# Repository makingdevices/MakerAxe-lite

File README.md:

<!-- Improved compatibility of back to top link: See: https://github.com/othneildrew/Best-README-Template/pull/73 -->

<!--
*** Thanks for checking out the Best-README-Template. If you have a suggestion
*** that would make this better, please fork the repo and create a pull request
*** or simply open an issue with the tag "enhancement".
*** Don't forget to give the project a star!
*** Thanks again! Now go create something AMAZING! :D
-->

<!-- PROJECT SHIELDS -->
<!--
*** I'm using markdown "reference style" links for readability.
*** Reference links are enclosed in brackets [ ] instead of parentheses ( ).
*** See the bottom of this document for the declaration of the reference variables
*** for contributors-url, forks-url, etc. This is an optional, concise syntax you may use.
*** https://www.markdownguide.org/basic-syntax/#reference-style-links
-->
[![Instagram][ig-shield]][ig-url]
[![Instagram][yt-shield]][yt-url]
[![PCBWAY][sponsor-shield]][sponsor-url]
[![Stargazers][stars-shield]][stars-url]
[![Issues][issues-shield]][issues-url]
[![LinkedIn][linkedin-shield]][linkedin-url]

<!-- PROJECT LOGO -->
<br />
<div align="center">

<h3 align="center">Making Devices</h3>

  <p align="center">
    Open Source projects where we struggle with engineering, electronics, coding and who knows what else... MakerAxe-lite is the foundation for new BTC miners and exciting hardware in the future. 
  </p>
</div>

<!-- TABLE OF CONTENTS -->
<details>
  <summary>Table of Contents</summary>
  <ol>
    <li>
      <a href="#about-the-project">About The Project</a>
      <ul>
        <li><a href="#built-with">Built With</a></li>
      </ul>
    </li>
    <li>
      <a href="#Build-one">Build one</a>
      <ul>
      </ul>
    </li>
    <li><a href="#goals">Goals</a></li>
    <li><a href="#features">Features</a></li>
    <li><a href="#roadmap">Roadmap</a></li>
    <li><a href="#license">License</a></li>
    <li><a href="#contact">Contact</a></li>
    <li><a href="#tools">Tools</a></li>
    <li><a href="#Sponsor">Sponsor</a></li>
  </ol>
</details>

<!-- ABOUT THE PROJECT -->
## About The Project

[![Bytes Counter Shot][product-screenshot]](https://makingdevices.com/)

```
Open Source is Intrinsic to Bitcoin
```

This is the motto you will see at the top of the [Bitaxe repository](https://github.com/skot/bitaxe), and it’s the reason Why MakerAxe-Lite was created.

MakerAxe Lite is the first attempt to extract the essentials of Bitaxe, reduce it to the minimum, and create a foundation for building new and exciting hardware in the future.

The project modifies the original hardware with the following changes:

1. The screen is not needed, as you now have AxeOS. Therefore, the screen will be removed (DNP) to reduce energy consumption and costs.
2. The 4-layer PCB is reduced to a 2-layer PCB, decreasing the cost of the PCB.
3. The 5V barrel input connector is replaced with USB PD. The voltage (20V, 15V, or 12V) is yet to be decided. This change ensures compatibility with recycled and reused phone or laptop chargers.
4. A LED has been added for blinking status and debug purposes.
5. Software compatibility with the stock [ESP-miner AxeOS](https://github.com/skot/ESP-Miner) (aside from the LED indicator).

<p align="right">(<a href="#readme-top">back to top</a>)</p>

### Built With

[![Microcontroller][ESP32]][ESP32-url]

[![Kicad][kicad-shield]][kicad-url]
[![SPONSOR][sponsor-icon]][sponsor-url]

<p align="right">(<a href="#readme-top">back to top</a>)</p>

<!-- GETTING STARTED -->

## Build one
The project is yet to be finished. Should you want to reproduce it, be careful. 

1. Get the gerber files for the latest version: [MakerAxe-lite V025](/Gerber/makeraxe-litev025.zip) 
2. Send them to a PCB manufacturer ([Our Sponsor is PCBWAY][sponsor-url])
3. Schematic (?)

YET TO BE COMPLETED.

<p align="right">(<a href="#readme-top">back to top</a>)</p>

<!-- GOALS -->
## Goals
- **Standalone**: can mine directly to your pool over WiFi. No External computer needed.
- **Embedded**: low cost, low maintenance, high availability, high reliability, low power.
- **ASIC**: based on the very, very efficient BM1366 from Bitmain.
- **Versatile**: solo/pool mining, autotune power/heat/efficiency.
- **Open Source**: All design files are provided.

<p align="right">(<a href="#readme-top">back to top</a>)</p>

<!-- FEATURES -->
## Features
- **ESP32-S3-WROOM-1** wifi microcontroller on board
- **TI TPS40305** buck regulator steps down the input voltage to power the BM1366
- **Maxim DS4432U+** current DAC digitally adjusts the BM1366 core voltage from 0.04V to 2.4V
- **TI INA260** power meter measures the input voltage and current of the miner
- **Microchip EMC2101** PWM controls the fan and monitors tach output. BM1366 doesn't support die temp, but we have it placed super close to the ASIC so we can use the internal temp feature.
- Enjoy :D!

<p align="right">(<a href="#readme-top">back to top</a>)</p>

<!-- ROADMAP -->
## Roadmap

- [X] Design the V025 prototype board.
- [ ] Complete the schematic and BoM files with LCSC&DK codes. 
- [ ] Order/Assembly the V025 prototype board.
- [ ] Validate V025 revision
  - [ ] Check that USB PD Works (12V, 15V, 20V)
  - [ ] Check the ESP32 can be programmed. 
  - [ ] AxeOS Self-testing is OK.
  - [ ] Solder the ASIC and check temperatures.
  - [ ] Characterize the overall efficiency.
  - [ ] Stress the buck converter to see if it is enough for next projects.
  - [ ] Explore alternatives to eliminate 5V rail.
  - [ ] Develop firmware so the LED can be used. Merge to ESP-miner if possible
- [ ] Validate the complete design + order PCBA 

See the [open issues](https://github.com/makingdevices/MakerAxe-lite/issues) for a full list of proposed features (and known issues).

State: Project <b>ONGOING</b> - 26/12/2024

Priority: <b>High</b>

<p align="right">(<a href="#readme-top">back to top</a>)</p>

<!-- LICENSE -->
## License

Distributed under three licenses:
- [Hardware](/License/HW_cern_ohl_s_v2.pdf)
- [Software](/License/SW_GPLv3.0.txt)
- [Documentation](/License/Documentation_CC-BY-SA-4.0.txt)

OSHWA License: Not Finished

[![GPL v3 License][license-shield]][license-url] 
<p align="right">(<a href="#readme-top">back to top</a>)</p>

<!-- CONTACT -->
## Contact

Making Devices - [@MakingDevices](https://www.instagram.com/makingdevices/)

Project Link: [https://github.com/makingdevices/MakerAxe-lite](https://github.com/makingdevices/MakerAxe-lite)

Other Links: [LinkTree](https://makingdevices.com/links/)

<!-- Tools -->
## Tools

During the realization of this project, you may need tools to assemble the PCB, solder components, and more.

These are the tools we've tested and currently have in our lab, so feel free to check them out if needed. Keep in mind that, even if prices are the same, you can support us in continuing to develop projects like this through the Amazon Influencer Program. Thank you!

- Microscope for smd soldering: [LinkMicro 246ms](https://amzn.to/3ZMVvwG)
- My solder paste: [ChipQuik LowTemp](https://amzn.to/3ZPYBjz)
- My soldering station with power supply: [Yihua 853D](https://amzn.to/3DwH0Wh)

<!-- Sponsor -->
## Sponsors

[PCBWAY](https://www.pcbway.com/?from=makingdevices) is the most professional PCB manufacturer for prototyping and low-volume production to work with in the world. With more than a decade in the field, They are committed to meeting the needs of their customers from different industries in terms of quality, delivery, cost-effectiveness and any other demanding requests. As Sponsor of Making Devices, they will be in charge of all the PCBs for MDV, allowing both of us to grow together in a long term partnership. We hope you take them into account for your both personal and professional prototypes or products.

[![Sponsor Shot][sponsor-pcb-1]][sponsor-url]

<p align="right">(<a href="#readme-top">back to top</a>)</p>

<!-- MARKDOWN LINKS & IMAGES -->
<!-- https://www.markdownguide.org/basic-syntax/#reference-style-links -->
[contributors-shield]: https://img.shields.io/github/contributors/makingdevices/MakerAxe-lite.svg?style=for-the-badge
[contributors-url]: https://github.com/makingdevices/MakerAxe-lite/graphs/contributors
[forks-shield]: https://img.shields.io/github/forks/makingdevices/MakerAxe-lite.svg?style=for-the-badge
[forks-url]: https://github.com/makingdevices/MakerAxe-lite/network/members
[stars-shield]: https://img.shields.io/github/stars/makingdevices/MakerAxe-lite.svg?style=for-the-badge
[stars-url]: https://github.com/makingdevices/MakerAxe-lite/stargazers
[issues-shield]: https://img.shields.io/github/issues/makingdevices/MakerAxe-lite.svg?style=for-the-badge
[issues-url]: https://github.com/makingdevices/MakerAxe-lite/issues
[license-shield]: /images/license.png
[license-url]: https://github.com/makingdevices/MakerAxe-lite/tree/main/License
[linkedin-shield]: https://img.shields.io/badge/-LinkedIn-black.svg?style=for-the-badge&logo=linkedin&colorB=555
[linkedin-url]: https://www.linkedin.com/company/making-devices/
[sponsor-shield]: https://img.shields.io/badge/SPONSOR-PCBWAY-black.svg?style=for-the-badge&colorB=1200
[sponsor-url]: https://www.pcbway.com/?from=makingdevices
[sponsor-screenshot]: /images/PCB_sponsor.png
[sponsor-pcb-1]: /images/makeraxe_pcb1.jpg
[sponsor-wurth-1]: /images/wurth_1.gif
[sponsor-wurth-3]: /images/wurth_3.jpg
[sponsor-url-wurth]: https://www.we-online.com/en
[product-screenshot]: images/render_front_pcb.png
[ESP32]: https://img.shields.io/badge/ESP32_S3-7c0a02?style=for-the-badge
[ESP32-url]: https://www.espressif.com/sites/default/files/documentation/esp32-s3-wroom-1_wroom-1u_datasheet_en.pdf
[kicad-shield]: https://img.shields.io/badge/kicad-0b03fc?style=for-the-badge&logo=kicad&logoColor=white
[kicad-url]: https://www.kicad.org/
[YT-screenshot]: images/YT_assembly.PNG
[sponsor-icon]:  https://img.shields.io/badge/-PCBWAY-black.svg?style=for-the-badge&colorB=1200
[ig-shield]: https://img.shields.io/badge/instagram-a83297?style=for-the-badge&logo=instagram&logoColor=white
[ig-url]: https://www.instagram.com/makingdevices/
[yt-shield]: https://img.shields.io/badge/youtube-ff0000?style=for-the-badge&logo=youtube&logoColor=white
[yt-url]: https://www.youtube.com/@MakingDevices
[MPLAB-C]: https://img.shields.io/badge/MPLAB%20C18-DD0031?style=for-the-badge&logo=C&logoColor=white
[Arduino]: https://img.shields.io/badge/ARDUINO-00878F?style=for-the-badge&logo=arduino&logoColor=white
[wurth-icon]: https://img.shields.io/badge/Wurth%20elektronik-FF0031?style=for-the-badge&logoColor=white
[Arduino-url]: https://www.arduino.cc/
[MPLAB-C-url]: https://www.microchip.com/en-us/development-tool/SW006011
[Svelte.dev]: https://img.shields.io/badge/Svelte-4A4A55?style=for-the-badge&logo=svelte&logoColor=FF3E00
[Svelte-url]: https://svelte.dev/
[Laravel.com]: https://img.shields.io/badge/Laravel-FF2D20?style=for-the-badge&logo=laravel&logoColor=white
[Laravel-url]: https://laravel.com
[Bootstrap.com]: https://img.shields.io/badge/Bootstrap-563D7C?style=for-the-badge&logo=bootstrap&logoColor=white
[Bootstrap-url]: https://getbootstrap.com
[JQuery.com]: https://img.shields.io/badge/jQuery-0769AD?style=for-the-badge&logo=jquery&logoColor=white
[JQuery-url]: https://jquery.com

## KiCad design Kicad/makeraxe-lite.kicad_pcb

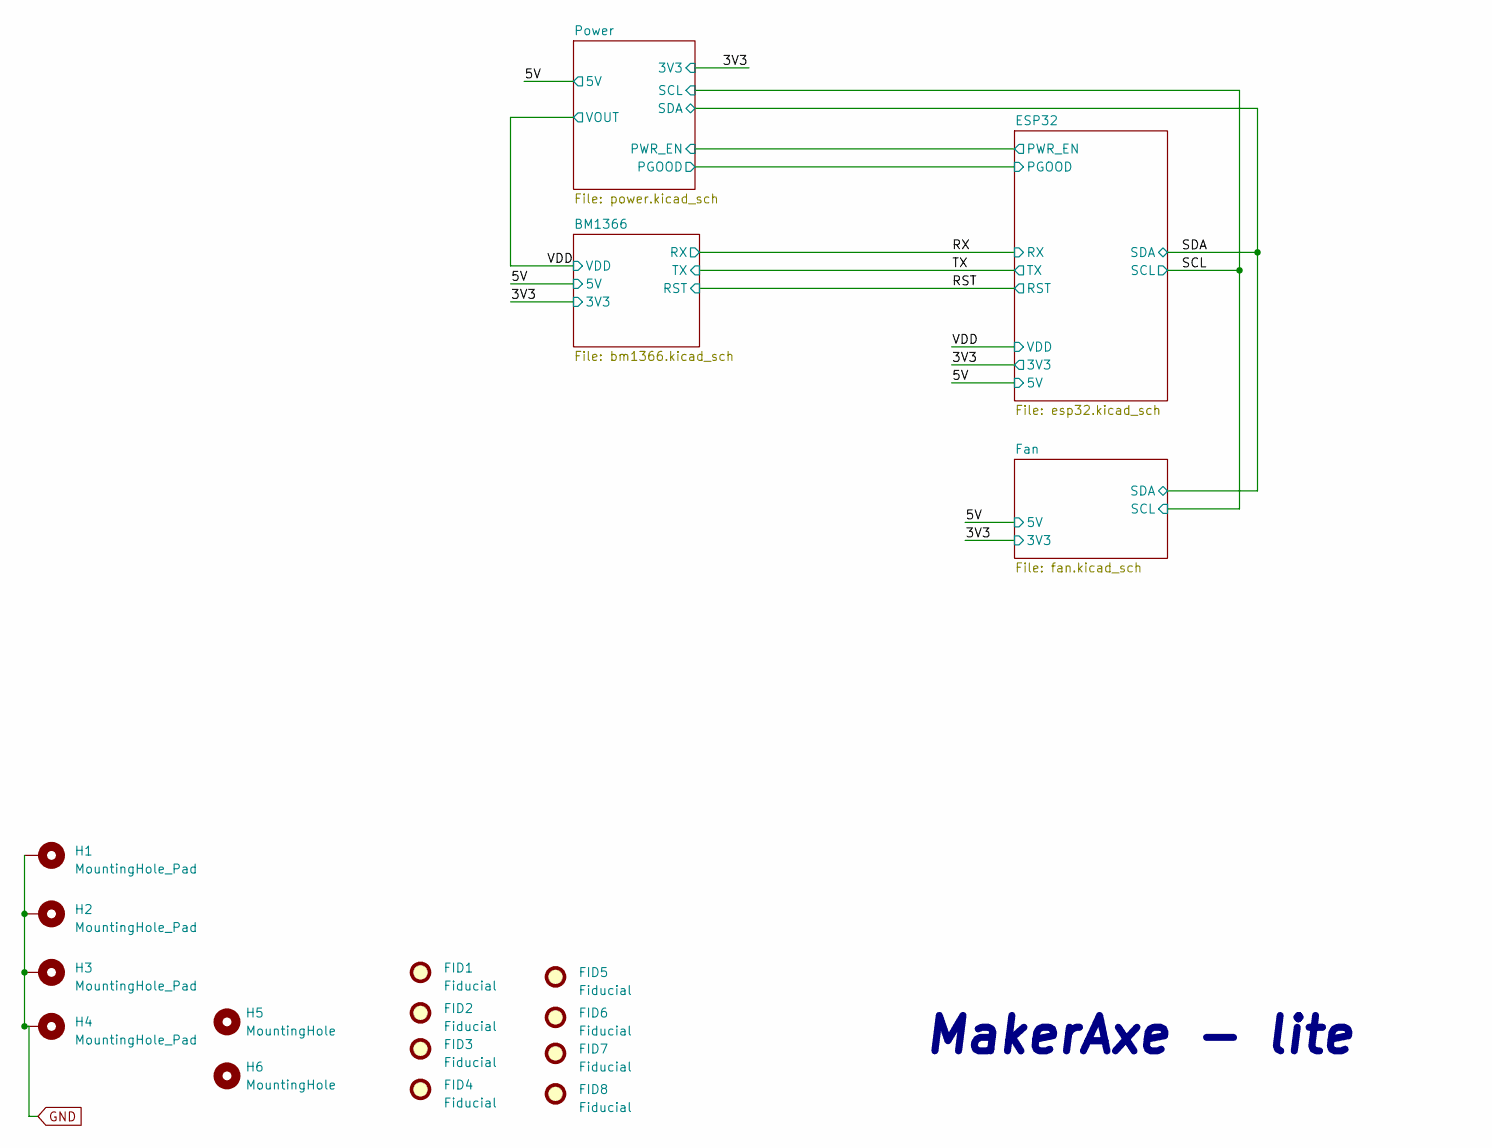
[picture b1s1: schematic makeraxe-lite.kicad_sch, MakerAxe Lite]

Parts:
FID1, FID2, FID3, FID4, FID5, FID6, FID7, FID8: Fiducial; Fiducial_1mm_Mask2mm
H1, H2, H3, H4: MountingHole_Pad; MountingHole_3mm_Pad_Via
H5, H6: MountingHole; MountingHole_3.5mm

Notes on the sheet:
MakerAxe - lite

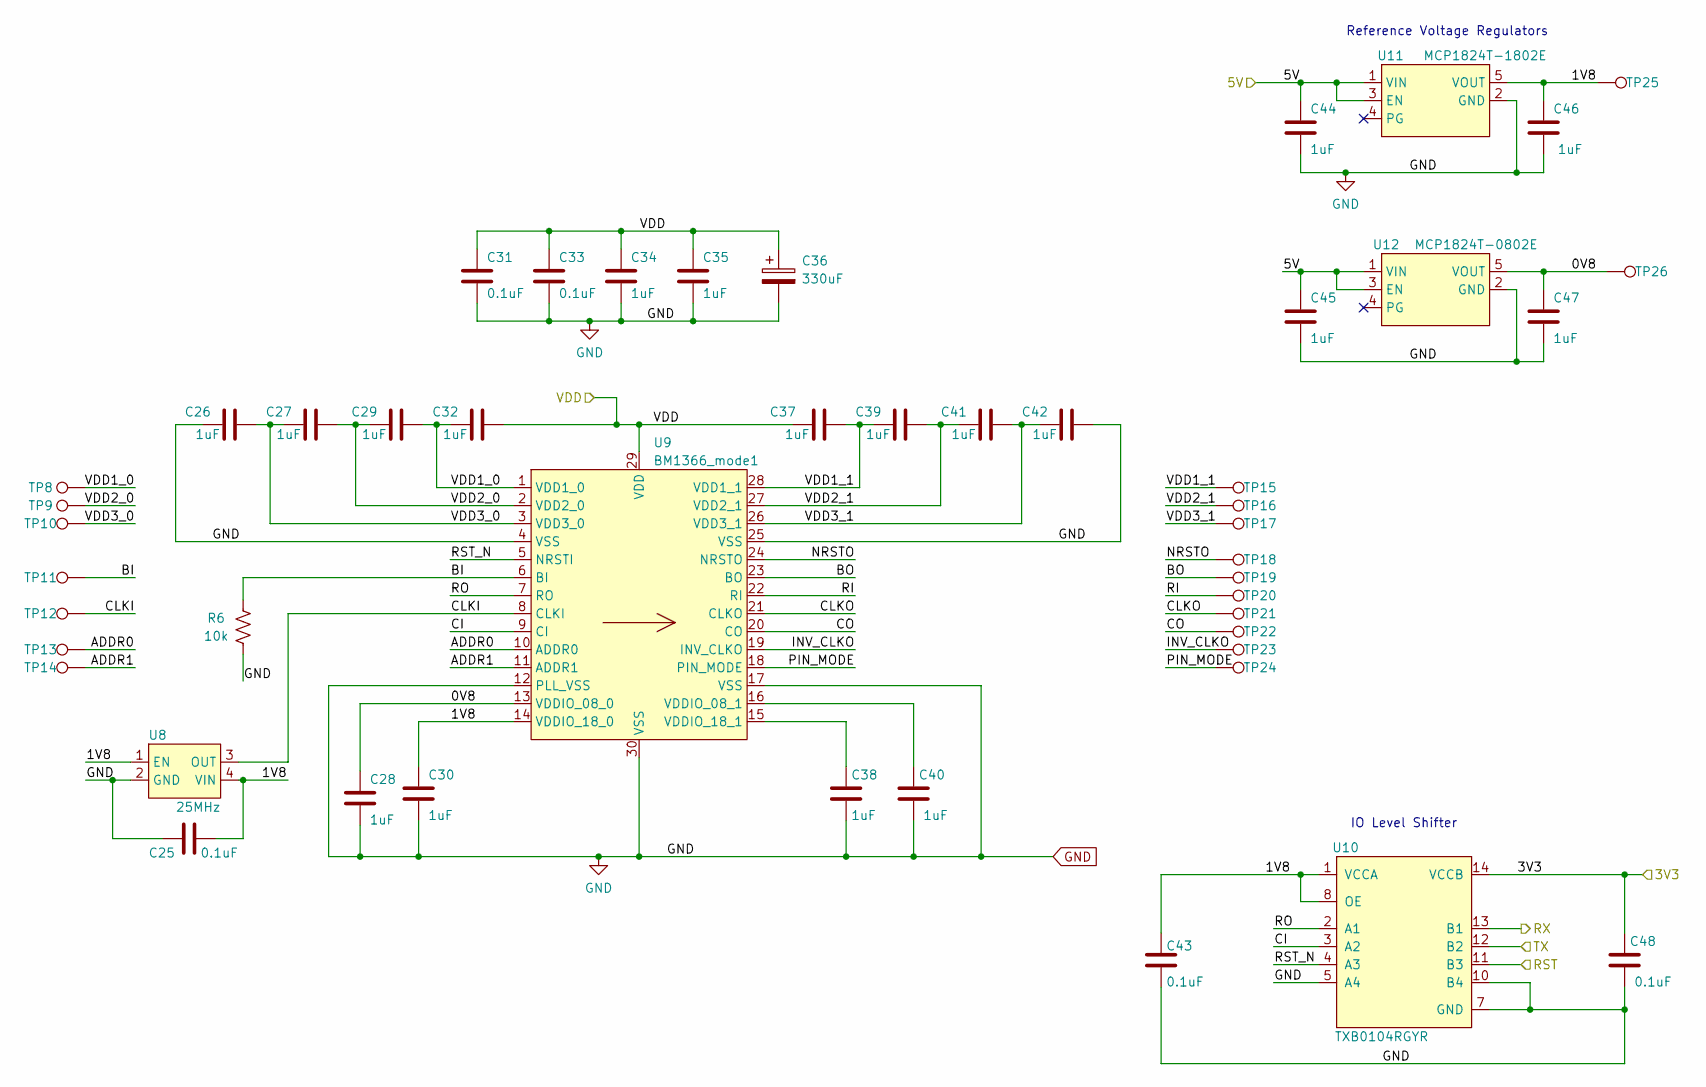
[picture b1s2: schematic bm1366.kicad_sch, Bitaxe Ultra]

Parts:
C25, C31, C33, C43, C48: 0.1uF; C_0402_1005Metric; PARTNO 0402X104K100CT
C26, C27, C28, C29, C30, C32, C34, C35, C37, C38, C39, C40, C41, C42, C44, C45, C46, C47: 1uF; C_0402_1005Metric; PARTNO EMK105BJ105MV-F
C36: 330uF; CP_EIA-7343-31_Kemet-D_Pad2.25x2.55mm_HandSolder; PARTNO 293D337X9010E2TE3
R6: 10k; R_0402_1005Metric; PARTNO RC0402JR-0710KL
TP8, TP9, TP10, TP11, TP12, TP13, TP14, TP15, TP16, TP17, TP18, TP19, TP20, TP21, TP22, TP23, TP24, TP25, TP26: TestPoint; TestPoint_Pad_D1.5mm
U8: 25MHz; O 25,0-JO32-B-1V3-1-T1-LF; PARTNO O 25,0-JO32-B-1V3-1-T1-LF
U9: BM1366_mode1; BM1366
U10: TXB0104RGYR; TXB0104; PARTNO TXB0104RGYR
U11: MCP1824T-1802E; SOT-23-5; PARTNO MCP1824T-1802E/OT
U12: MCP1824T-0802E; SOT-23-5; PARTNO MCP1824T-0802E/OT

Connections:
/3V3: C48.1, U10.14 (VCCB); also elsewhere on the board
/5V: C44.1, C45.1, U11.1 (VIN), U11.3 (EN), U12.1 (VIN), U12.3 (EN); also elsewhere on the board
/BM1366/0V8: C28.1, C47.1, TP26.1, U9.13 (VDDIO_08_0), U12.5 (VOUT)
/BM1366/1V8: C25.2, C30.1, C43.1, C46.1, TP25.1, U8.1 (EN), U8.4 (VIN), U9.14 (VDDIO_18_0), U10.1 (VCCA), U10.8 (OE), U11.5 (VOUT)
/BM1366/ADDR0: TP13.1, U9.10 (ADDR0)
/BM1366/ADDR1: TP14.1, U9.11 (ADDR1)
/BM1366/BO: TP19.1, U9.23 (BO)
/BM1366/CI: U9.9 (CI), U10.3 (A2)
/BM1366/CLKI: TP12.1, U8.3 (OUT), U9.8 (CLKI)
/BM1366/CLKO: TP21.1, U9.21 (CLKO)
/BM1366/CO: TP22.1, U9.20 (CO)
/BM1366/INV_CLKO: TP23.1, U9.19 (INV_CLKO)
/BM1366/NRSTO: TP18.1, U9.24 (NRSTO)
/BM1366/PIN_MODE: TP24.1, U9.18 (PIN_MODE)
/BM1366/RI: TP20.1, U9.22 (RI)
/BM1366/RO: U9.7 (RO), U10.2 (A1)
/BM1366/RST_N: U9.5 (NRSTI), U10.4 (A3)
/BM1366/VDD1_0: C29.2, C32.1, TP8.1, U9.1 (VDD1_0)
/BM1366/VDD1_1: C37.2, C39.1, TP15.1, U9.28 (VDD1_1)
/BM1366/VDD2_0: C27.2, C29.1, TP9.1, U9.2 (VDD2_0)
/BM1366/VDD2_1: C39.2, C41.1, TP16.1, U9.27 (VDD2_1)
/BM1366/VDD3_0: C26.2, C27.1, TP10.1, U9.3 (VDD3_0)
/BM1366/VDD3_1: C41.2, C42.1, TP17.1, U9.26 (VDD3_1)
/RST: U10.11 (B3); also elsewhere on the board
/RX: U10.13 (B1); also elsewhere on the board
/TX: U10.12 (B2); also elsewhere on the board
unnamed: C40.1, U9.16 (VDDIO_08_1)
unnamed: C38.1, U9.15 (VDDIO_18_1)

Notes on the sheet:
Reference Voltage Regulators
IO Level Shifter

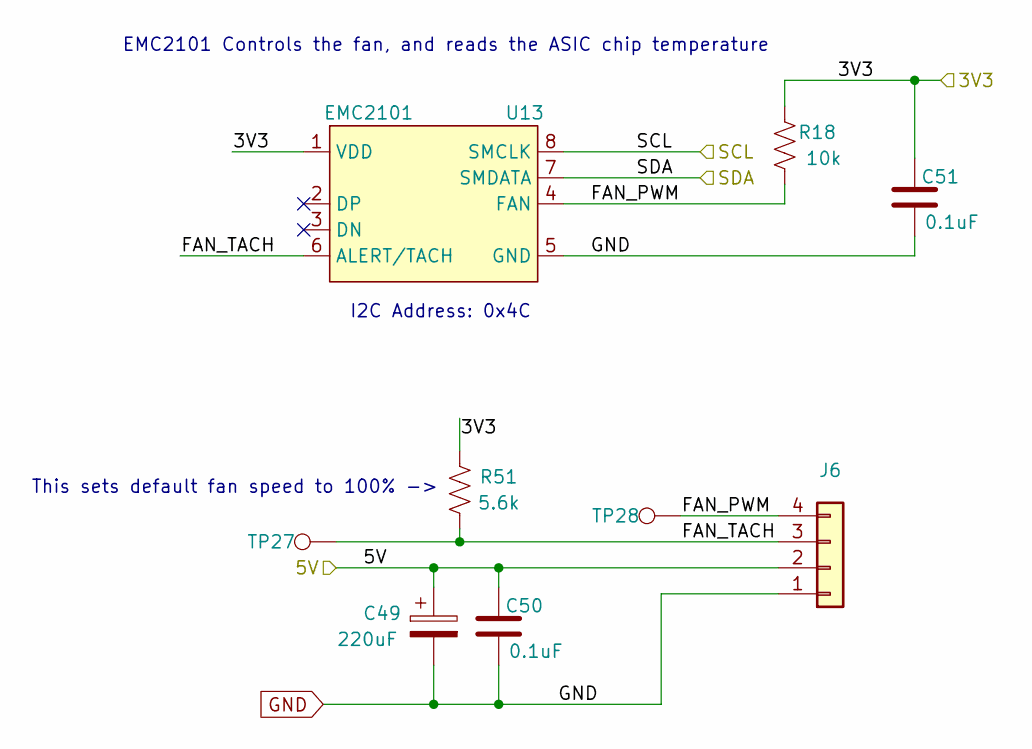
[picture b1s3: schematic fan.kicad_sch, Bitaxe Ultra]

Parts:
C49: 220uF; CP_Elec_6.3x7.7; PARTNO 865080345012
C50, C51: 0.1uF; C_0402_1005Metric; PARTNO 0402X104K100CT
J6: Conn_01x04; 470531000; PARTNO 0470531000
R18: 10k; R_0402_1005Metric; PARTNO RC0402JR-0710KL
R51: 5.6k; R_0402_1005Metric; PARTNO RC0402FR-135K6L
TP27, TP28: TestPoint; TestPoint_Pad_D1.5mm
U13: EMC2101; TSSOP-8_3x3mm_P0.65mm; PARTNO EMC2101-R-ACZL-TR

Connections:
/3V3: C51.1, R18.2, U13.1 (VDD); also elsewhere on the board
/5V: C49.1, C50.1, J6.2; also elsewhere on the board
/Fan/FAN_PWM: J6.4, R18.1, TP28.1, U13.4 (FAN)
/Fan/FAN_TACH: J6.3, TP27.1, U13.6 (ALERT/TACH); also elsewhere on the board
/SCL: U13.8 (SMCLK); also elsewhere on the board
/SDA: U13.7 (SMDATA); also elsewhere on the board

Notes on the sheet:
EMC2101 Controls the fan, and reads the ASIC chip temperature
This sets default fan speed to 100% ->
I2C Address: 0x4C

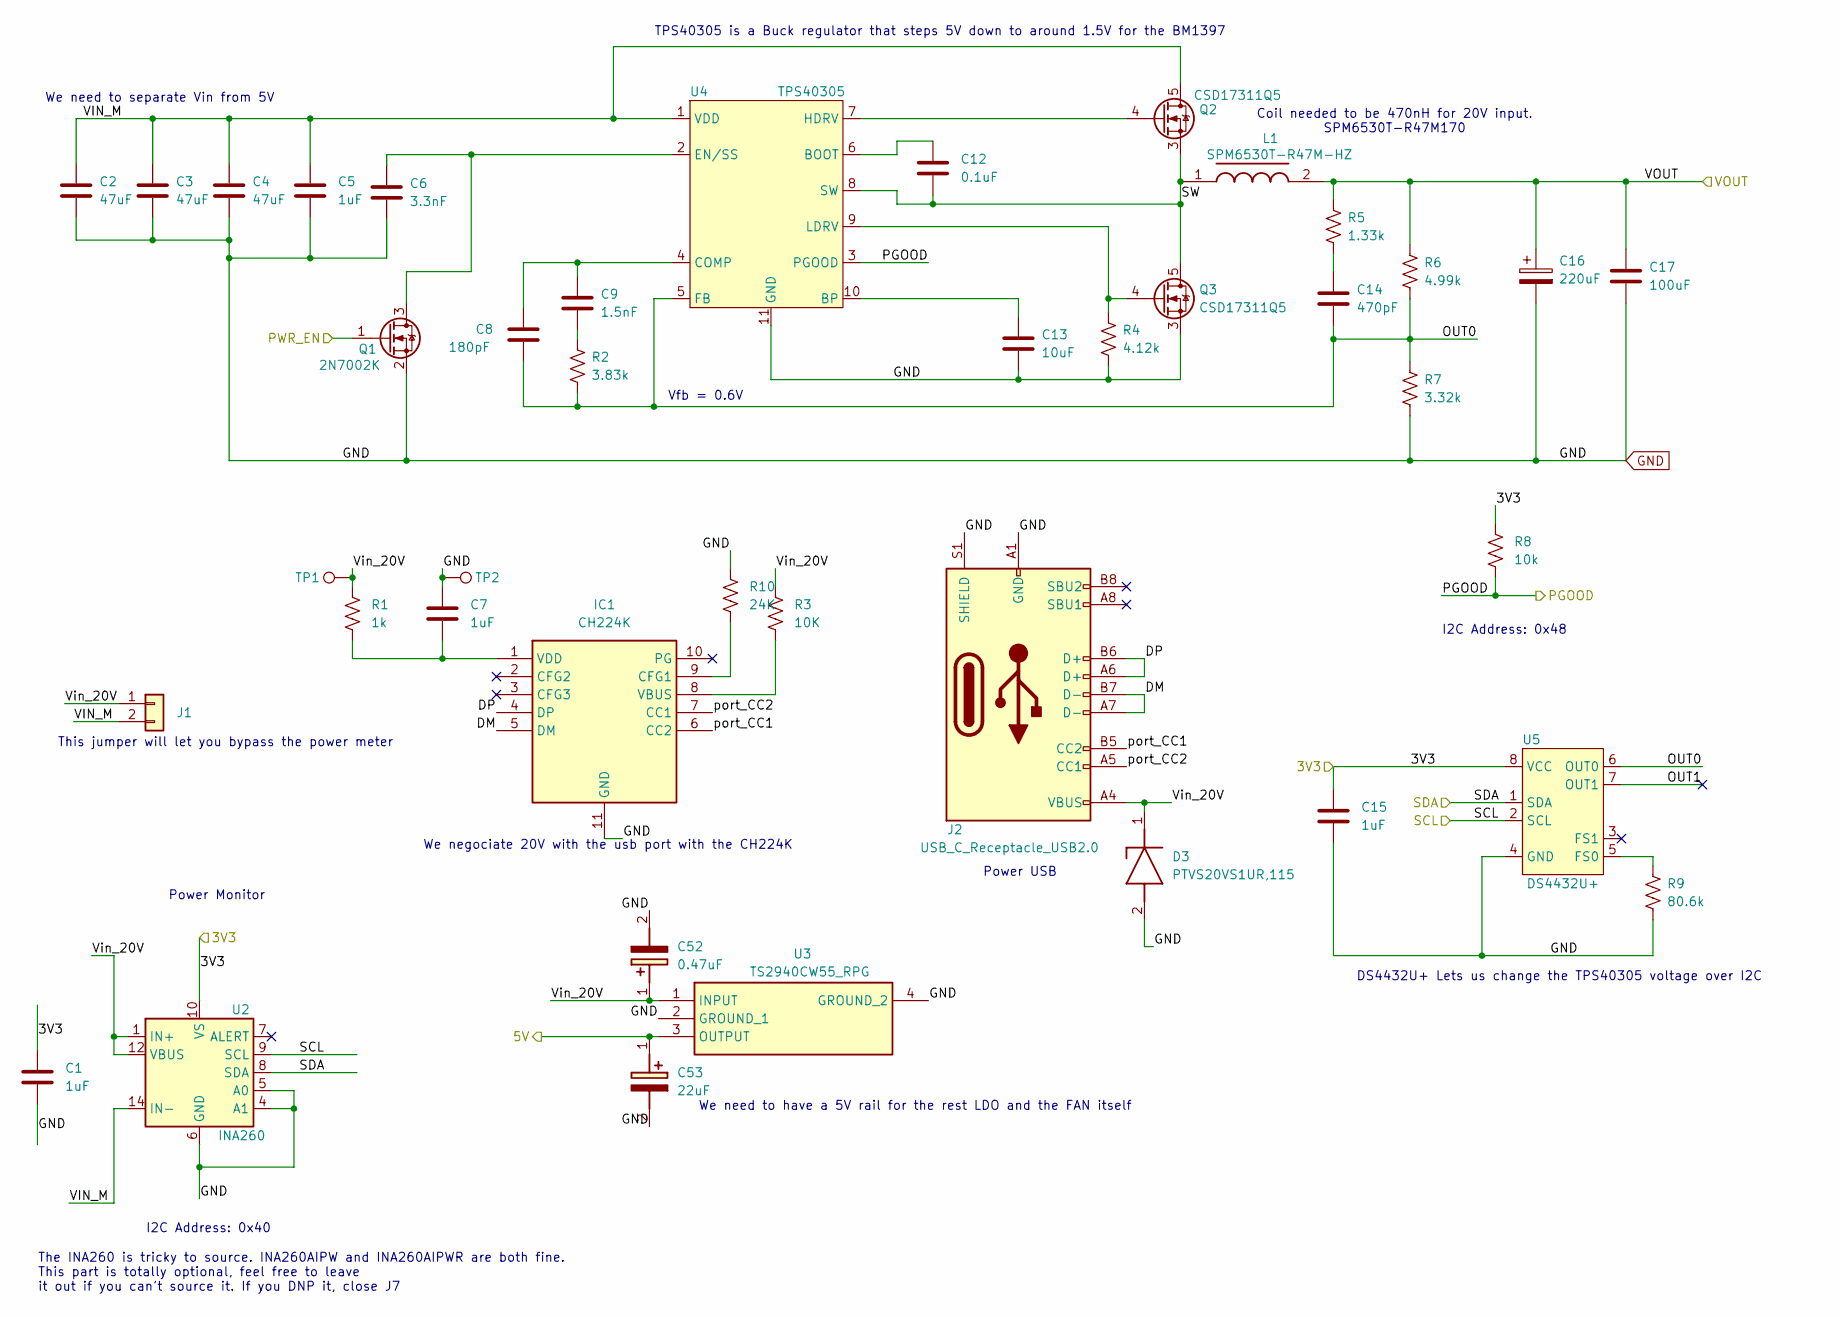
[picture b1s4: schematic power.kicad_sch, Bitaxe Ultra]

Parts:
C1, C15: 1uF; C_0402_1005Metric; PARTNO EMK105BJ105MV-F
C2, C3, C4: 47uF; C_1210_3225Metric; PARTNO GRM32ER61C476KE15L
C5, C7: 1uF; C_0805_2012Metric; PARTNO CL21B105KOFNNNG
C6: 3.3nF; C_0402_1005Metric; PARTNO CL05B332KB5NNNC
C8: 180pF; C_0805_2012Metric; PARTNO CC0805JRNPO9BN181
C9: 1.5nF; C_0805_2012Metric; PARTNO CC0805KRX7R9BB152
C12: 0.1uF; C_0402_1005Metric; PARTNO 0402X104K100CT
C13: 10uF; C_0805_2012Metric; PARTNO CL21A106KOQNNNE
C14: 470pF; C_0805_2012Metric; PARTNO 0805B471K500CT
C16: 220uF; CAP_2R5TPE220MAFB; PARTNO 2R5TPE220MAFB
C17: 100uF; C_1206_3216Metric; PARTNO C3216X5R0J107M160AB
C52: 0.47uF; T491A; Mouser Part Number 80-T491A474K025AT
C53: 22uF; T495C; Mouser Part Number 80-T495C226K25E300
D3: PTVS20VS1UR,115; SOD123W; Mouser Part Number 771-PTVS20VS1UR115
IC1: CH224K; SOP100P600X180-11N; Manufacturer_Part_Number CH224K
J1: Conn_01x02; PinHeader_1x02_P2.54mm_Vertical
J2: USB_C_Receptacle_USB2.0; USB_C_Receptacle_GCT_USB4105-xx-A_16P_TopMnt_Horizontal; PARTNO USB4105-GF-A
L1: SPM6530T-R47M-HZ; SPM6530; Mouser Part Number 810-SPM6530T-R47M-HZ
Q1: 2N7002K; SOT-323_SC-70; PARTNO 2N7002KW
Q2, Q3: CSD17311Q5; PARTNO CSD17311Q5
R1: 1k; R_0402_1005Metric; PARTNO RC0402FR-073K83L
R2: 3.83k; R_0402_1005Metric; PARTNO RC0402FR-073K83L
R3: 10K; R_0402_1005Metric; PARTNO RC0402FR-073K83L
R4: 4.12k; R_0402_1005Metric; PARTNO RMCF0402FT4K12
R5: 1.33k; R_0402_1005Metric; PARTNO RC0402FR-071K33L
R6: 4.99k; R_0402_1005Metric; PARTNO RC0402FR-074K99L
R7: 3.32k; R_0402_1005Metric; PARTNO RC0402FR-073K32L
R8: 10k; R_0402_1005Metric; PARTNO RC0402JR-0710KL
R9: 80.6k; R_0402_1005Metric; PARTNO RC0402FR-0780K6L
R10: 24K; R_0402_1005Metric; PARTNO RC0402FR-073K83L
TP1, TP2: TestPoint; TestPoint_Pad_D1.5mm
U2: INA260; TSSOP-16_4.4x5mm_P0.65mm; PARTNO INA260AIPW
U3: TS2940CW55_RPG; TO-263-3_TabPin2; Mouser Part Number 821-TS2940CW33RPG
U4: TPS40305; PARTNO TPS40305DRCR
U5: DS4432U+; TSSOP-8_3x3mm_P0.65mm; PARTNO DS4432U+

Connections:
/3V3: C1.1, C15.1, R8.1, U2.10 (VS), U5.8 (VCC); also elsewhere on the board
/5V: C53.1 (+), U3.3 (OUTPUT); also elsewhere on the board
/ESP32/PWR_EN: Q1.1 (G); also elsewhere on the board
/Power/DM: IC1.5 (DM), J2.A7 (D-), J2.B7 (D-)
/Power/DP: IC1.4 (DP), J2.A6 (D+), J2.B6 (D+)
/Power/OUT1: U5.7 (OUT1)
/Power/PGOOD: R8.2, U4.3 (PGOOD); also elsewhere on the board
/Power/SW: C12.2, L1.1, Q2.1, Q2.2, Q2.3 (S), Q3.5 (D), U4.8 (SW)
/Power/VIN_M: C2.1, C3.1, C4.1, C5.1, J1.2, Q2.5 (D), U2.14 (IN-), U2.15 (IN-), U2.16 (IN-), U4.1 (VDD)
/Power/Vin_20V: C52.1 (+), D3.1 (K), J1.1, J2.A4 (VBUS), J2.A9 (VBUS), J2.B4 (VBUS), J2.B9 (VBUS), R1.1, R3.1, TP1.1, U2.1 (IN+), U2.2 (IN+), U2.3 (IN+), U2.12 (VBUS), U3.1 (INPUT)
/Power/port_CC1: IC1.6 (CC2), J2.B5 (CC2)
/Power/port_CC2: IC1.7 (CC1), J2.A5 (CC1)
/SCL: U2.9 (SCL), U5.2 (SCL); also elsewhere on the board
/SDA: U2.8 (SDA), U5.1 (SDA); also elsewhere on the board
unnamed: C9.2, R2.1
unnamed: C14.1, R5.2
unnamed: IC1.9 (CFG1), R10.2
unnamed: IC1.8 (VBUS), R3.2
unnamed: C7.2, IC1.1 (VDD), R1.2
unnamed: C6.1, Q1.3 (D), U4.2 (EN/SS)
unnamed: Q2.4 (G), U4.7 (HDRV)
unnamed: Q3.4 (G), R4.1, U4.9 (LDRV)
unnamed: C12.1, U4.6 (BOOT)
unnamed: C13.1, U4.10 (BP)
unnamed: C8.1, C9.1, U4.4 (COMP)
unnamed: R9.1, U5.5 (FS0)

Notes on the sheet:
DS4432U+ Lets us change the TPS40305 voltage over I2C
I2C Address: 0x48
The INA260 is tricky to source. INA260AIPW and INA260AIPWR are both fine. This part is totally optional, feel free to leave it out if you can't source it. If you DNP it, close J7
Power Monitor
Power USB
TPS40305 is a Buck regulator that steps 5V down to around 1.5V for the BM1397
We need to have a 5V rail for the rest LDO and the FAN itself
Coil needed to be 470nH for 20V input. SPM6530T-R47M170
I2C Address: 0x40
Vfb = 0.6V
This jumper will let you bypass the power meter
We negociate 20V with the usb port with the CH224K
We need to separate Vin from 5V

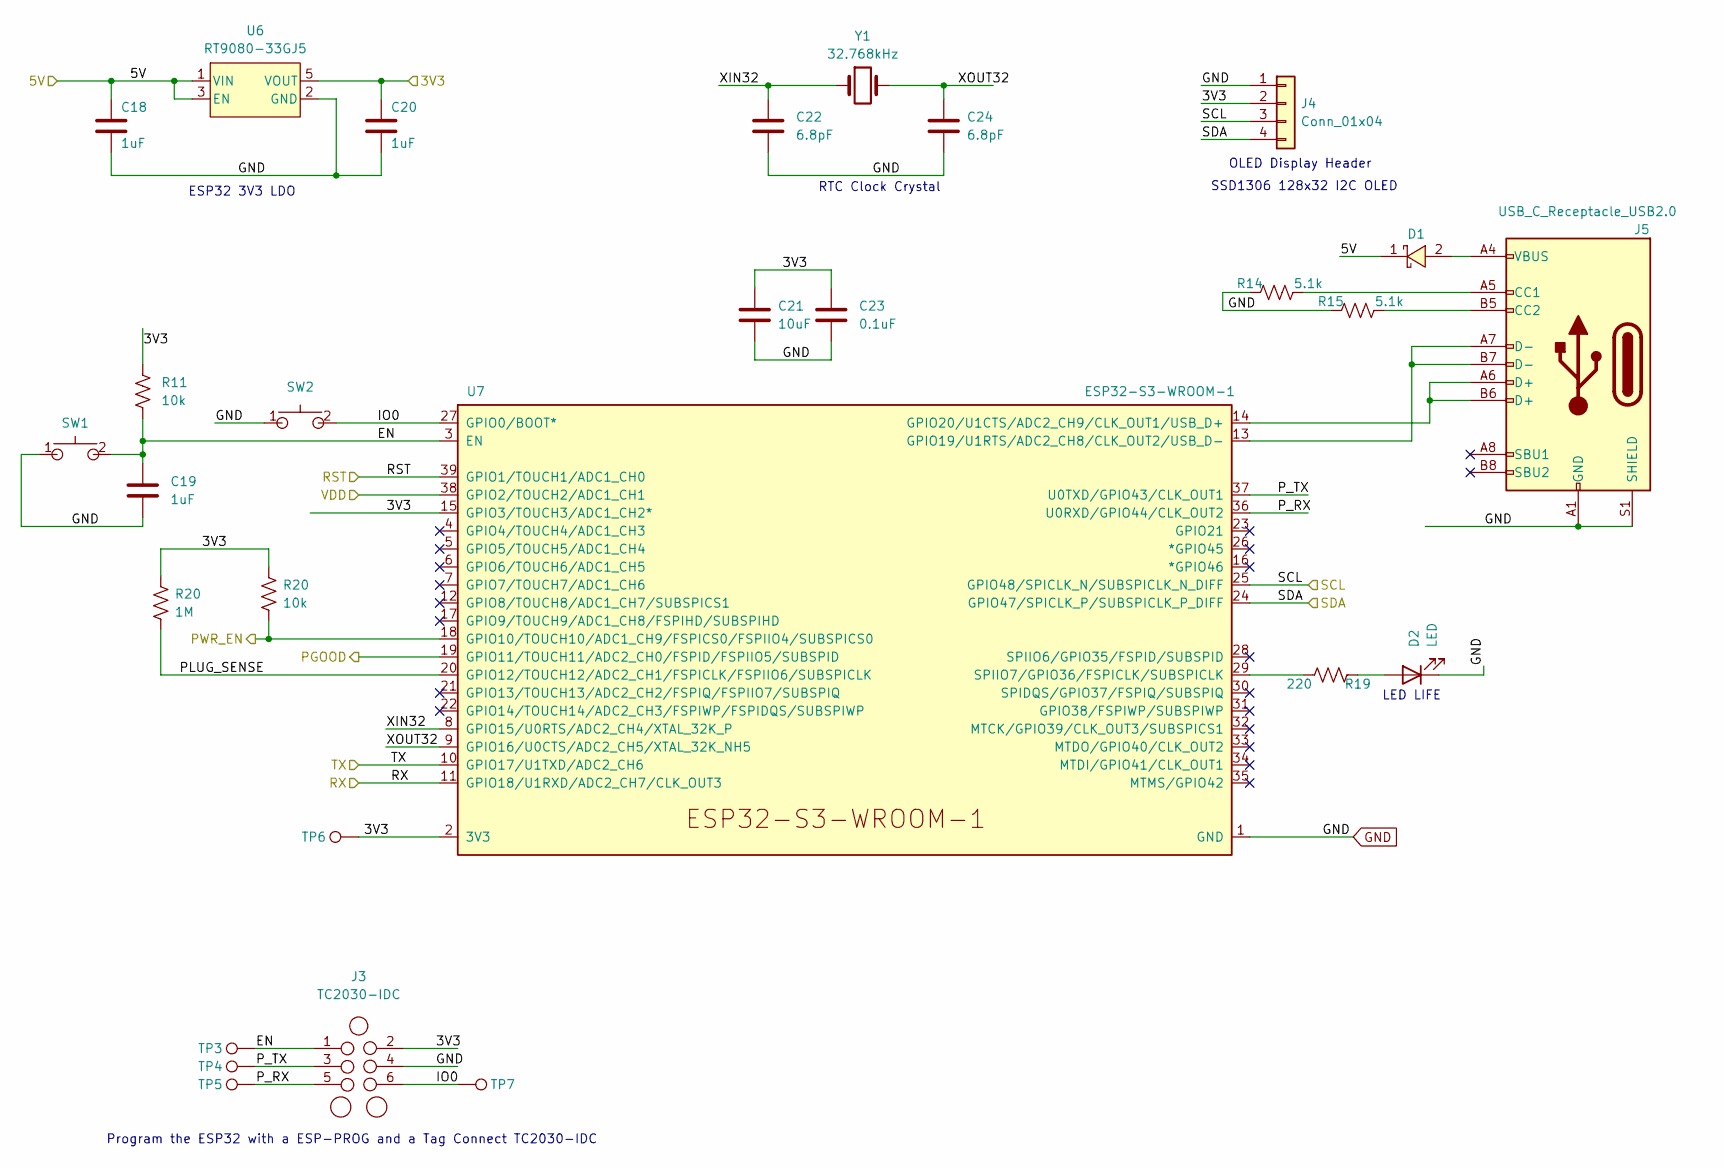
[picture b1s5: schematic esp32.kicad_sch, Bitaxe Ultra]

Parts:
C18, C19, C20: 1uF; C_0402_1005Metric; PARTNO EMK105BJ105MV-F
C21: 10uF; C_0805_2012Metric; PARTNO CL21A106KOQNNNE
C22, C24: 6.8pF; C_0402_1005Metric; PARTNO C0402C689C5GAC7867
C23: 0.1uF; C_0402_1005Metric; PARTNO 0402X104K100CT
D1: SS310; D_SMA; PARTNO SK310A-LTP
D2: LED; LED_0805_2012Metric_Pad1.15x1.40mm_HandSolder
J3: TC2030-IDC; Tag-Connect_TC2030-IDC-NL_2x03_P1.27mm_Vertical
J4: Conn_01x04; PinSocket_1x04_P2.54mm_Vertical_SMD_Pin1Right; PARTNO NPTC041KFXC-RC
J5: USB_C_Receptacle_USB2.0; USB_C_Receptacle_GCT_USB4105-xx-A_16P_TopMnt_Horizontal; PARTNO USB4105-GF-A
R11: 10k; R_0402_1005Metric; PARTNO RC0402JR-0710KL
R14, R15: 5.1k; R_0402_1005Metric; PARTNO RMCF0402JT5K10
R19: 220; R_0402_1005Metric; PARTNO RMCF0402JT5K10
R20: 1M; R_0402_1005Metric; PARTNO RC0402FR-071ML
SW1, SW2: GT-TC029B-H025-L1N; SW_CS1213AGF260_CRS; PARTNO CS1213AGF260
TP3, TP4, TP5, TP6, TP7: TestPoint; TestPoint_Pad_D1.5mm
U6: RT9080-33GJ5; PARTNO RT9080-33GJ5
U7: ESP32-S3-WROOM-1; PARTNO ESP32-S3-WROOM-1-N16R8
Y1: 32.768kHz; SC32S-7PF20PPM; PARTNO SC32S-7PF20PPM

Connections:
/3V3: C20.1, C21.1, C23.1, J3.2, J4.2, R11.1, TP6.1, U6.5 (VOUT), U7.2 (3V3), U7.15 (GPIO3/TOUCH3/ADC1_CH2*); also elsewhere on the board
/5V: C18.1, D1.1, U6.1 (VIN), U6.3 (EN); also elsewhere on the board
/ESP32/EN: C19.1, J3.1, R11.2, SW1.2, TP3.1, U7.3 (EN)
/ESP32/IO0: J3.6, SW2.2, TP7.1, U7.27 (GPIO0/BOOT*)
/ESP32/PLUG_SENSE: U7.20 (GPIO12/TOUCH12/ADC2_CH1/FSPICLK/FSPIIO6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); also elsewhere on the board
/ESP32/PWR_EN: U7.18 (GPIO10/TOUCH10/ADC1_CH9/FSPICS0/FSPIIO4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); also elsewhere on the board
/ESP32/P_RX: J3.5, TP5.1, U7.36 (U0RXD/GPIO44/CLK_OUT2)
/ESP32/P_TX: J3.3, TP4.1, U7.37 (U0TXD/GPIO43/CLK_OUT1)
/ESP32/XIN32: C22.1, U7.8 (GPIO15/U0RTS/ADC2_CH4/XTAL_32K_P), Y1.1
/ESP32/XOUT32: C24.1, U7.9 (GPIO16/U0CTS/ADC2_CH5/XTAL_32K_NH5), Y1.2
/Power/PGOOD: U7.19 (GPIO11/TOUCH11/ADC2_CH0/FSPID/FSPIIO5/S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); also elsewhere on the board
/RST: U7.39 (GPIO1/TOUCH1/ADC1_CH0); also elsewhere on the board
/RX: U7.11 (GPIO18/U1RXD/ADC2_CH7/CLK_OUT3); also elsewhere on the board
/SCL: J4.3, U7.25 (GPIO48/SPICLK_N/SUBSPICLK_N_DIFF); also elsewhere on the board
/SDA: J4.4, U7.24 (GPIO47/SPICLK_P/SUBSPICLK_P_DIFF); also elsewhere on the board
/TX: U7.10 (GPIO17/U1TXD/ADC2_CH6); also elsewhere on the board
unnamed: D1.2, J5.A4 (VBUS), J5.A9 (VBUS), J5.B4 (VBUS), J5.B9 (VBUS)
unnamed: D2.2 (A), R19.1
unnamed: J5.A5 (CC1), R14.2
unnamed: J5.B5 (CC2), R15.2
unnamed: J5.A7 (D-), J5.B7 (D-), U7.13 (GPIO19/U1RTS/ADC2_CH8/CLK_OUT2/USB_D-)
unnamed: J5.A6 (D+), J5.B6 (D+), U7.14 (GPIO20/U1CTS/ADC2_CH9/CLK_OUT1/USB_D+)
unnamed: R19.2, U7.29 (SPIIO7/GPIO36/FSPICLK/SUBSPICLK)

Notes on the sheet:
RTC Clock Crystal
ESP32 3V3 LDO
Program the ESP32 with a ESP-PROG and a Tag Connect TC2030-IDC
SSD1306 128x32 I2C OLED
OLED Display Header
LED LIFE

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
